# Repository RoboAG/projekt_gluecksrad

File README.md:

# projekt_gluecksrad
Bau eines elektrischen Glücksrades für schulische Veranstaltungen

Hier gibt es eine kleines [Demo-Video](https://www.youtube.com/watch?v=hORIZUaodIo&list=PL4P27g8g4QtTZY6d-4PRqTHP1PGKIp_SS) und eine [Bedienungsanleitung](Software/Keplertag_2021/README.md)([pdf](Anleitung/Anleitung_Bedienung.pdf)).

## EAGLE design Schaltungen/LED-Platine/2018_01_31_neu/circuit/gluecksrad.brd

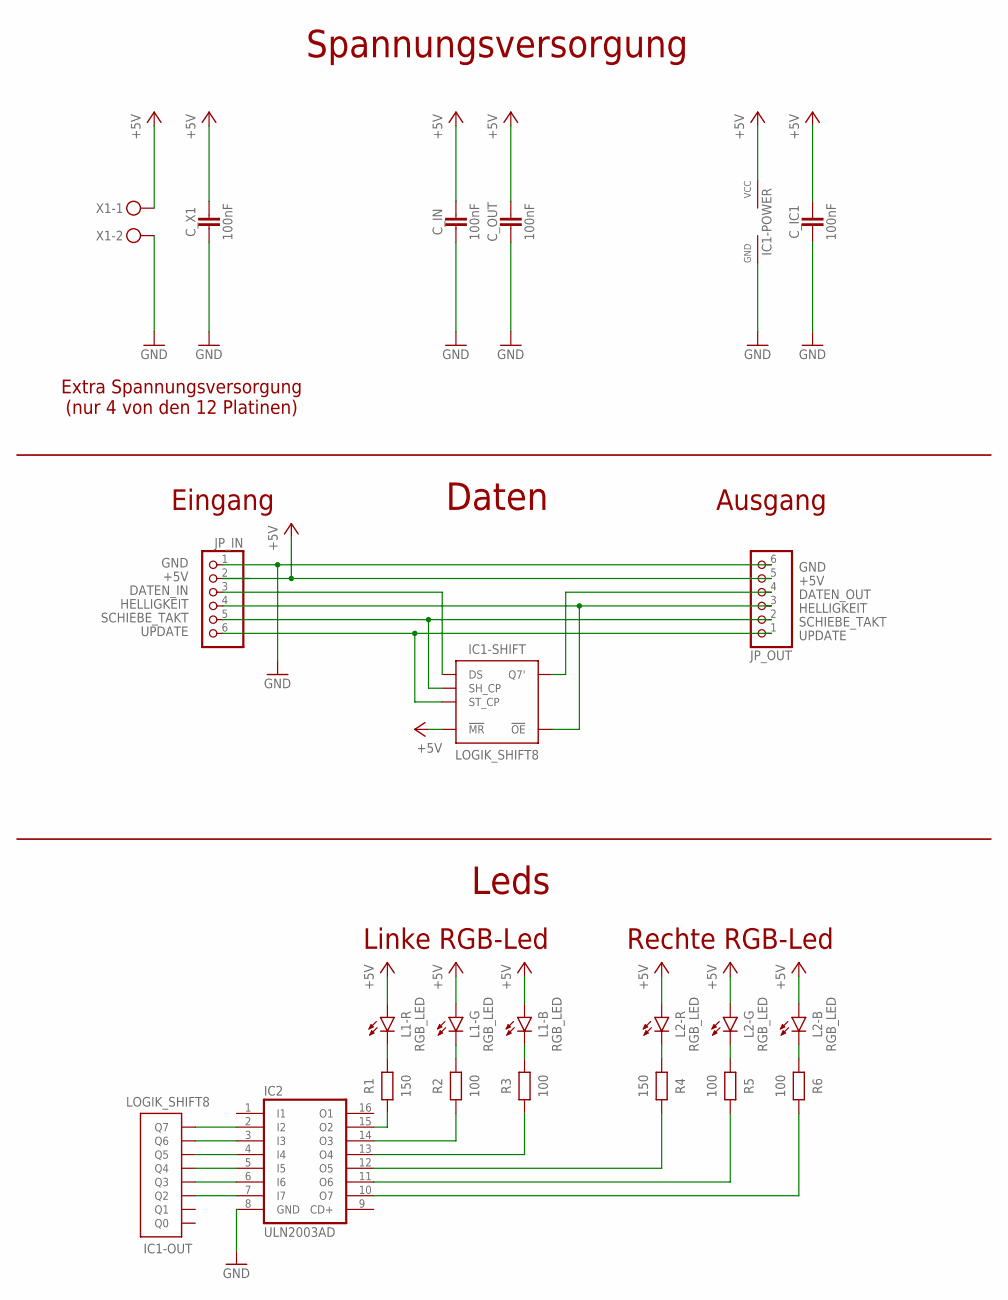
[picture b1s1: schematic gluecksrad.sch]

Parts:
C_IC1: 100nF; C_THT_2
C_IN: 100nF; C_THT_2
C_OUT: 100nF; C_THT_2
C_X1: 100nF; C_THT_2
IC1: LOGIK_SHIFT8; IC_SOIC16
IC2: ULN2003AD; SO16
JP_IN: PINHD-1X6/90; 1X06/90
JP_OUT: PINHD-1X6/90; 1X06/90
L1, L2: RGB_LED; LED_TOP_PLCC6
R1, R4: 150; R_THT_4
R2, R3, R5, R6: 100; R_THT_4
X1: STECKER_SPG_2

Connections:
+5V: C_IC1.1, C_IN.1, C_OUT.1, C_X1.1, IC1.P$10 (!MR), IC1.P$16 (VCC), JP_IN.2, JP_OUT.5, L1.1 (A), L1.3 (A), L1.4 (A), L2.1 (A), L2.3 (A), L2.4 (A), X1.1
DATEN_IN: IC1.P$14 (DS), JP_IN.3
DATEN_OUT: IC1.P$9 (Q7'), JP_OUT.4
GND: C_IC1.2, C_IN.2, C_OUT.2, C_X1.2, IC1.P$8 (GND), IC2.8 (GND), JP_IN.1, JP_OUT.6, X1.2
HELLIGKEIT: IC1.P$13 (!OE), JP_IN.4, JP_OUT.3
unnamed: IC1.P$5 (Q5), IC2.4 (I4)
unnamed: IC1.P$6 (Q6), IC2.3 (I3)
unnamed: IC1.P$2 (Q2), IC2.7 (I7)
unnamed: IC1.P$7 (Q7), IC2.2 (I2)
unnamed: IC1.P$3 (Q3), IC2.6 (I6)
unnamed: IC2.15 (O2), R1.2
unnamed: IC2.14 (O3), R2.2
unnamed: IC2.13 (O4), R3.2
unnamed: IC2.12 (O5), R4.1
unnamed: IC2.11 (O6), R5.1
unnamed: IC2.10 (O7), R6.1
unnamed: L1.6 (C), R1.1
unnamed: L1.2 (C), R2.1
unnamed: L1.5 (C), R3.1
unnamed: L2.6 (C), R4.2
unnamed: L2.2 (C), R5.2
unnamed: L2.5 (C), R6.2
unnamed: IC1.P$4 (Q4), IC2.5 (I5)
SCHIEBE_TAKT: IC1.P$11 (SH_CP), JP_IN.5, JP_OUT.2
UPDATE: IC1.P$12 (ST_CP), JP_IN.6, JP_OUT.1

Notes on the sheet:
Extra Spannungsversorgung (nur 4 von den 12 Platinen)
Eingang
Ausgang
Daten
Spannungsversorgung
Leds
Linke RGB-Led
Rechte RGB-Led

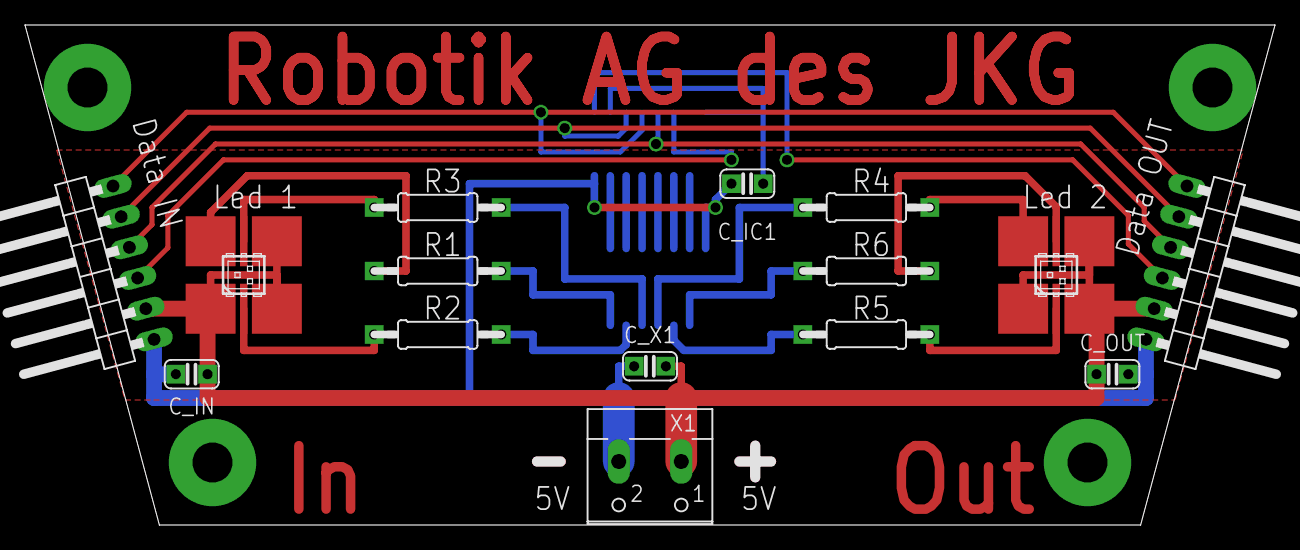
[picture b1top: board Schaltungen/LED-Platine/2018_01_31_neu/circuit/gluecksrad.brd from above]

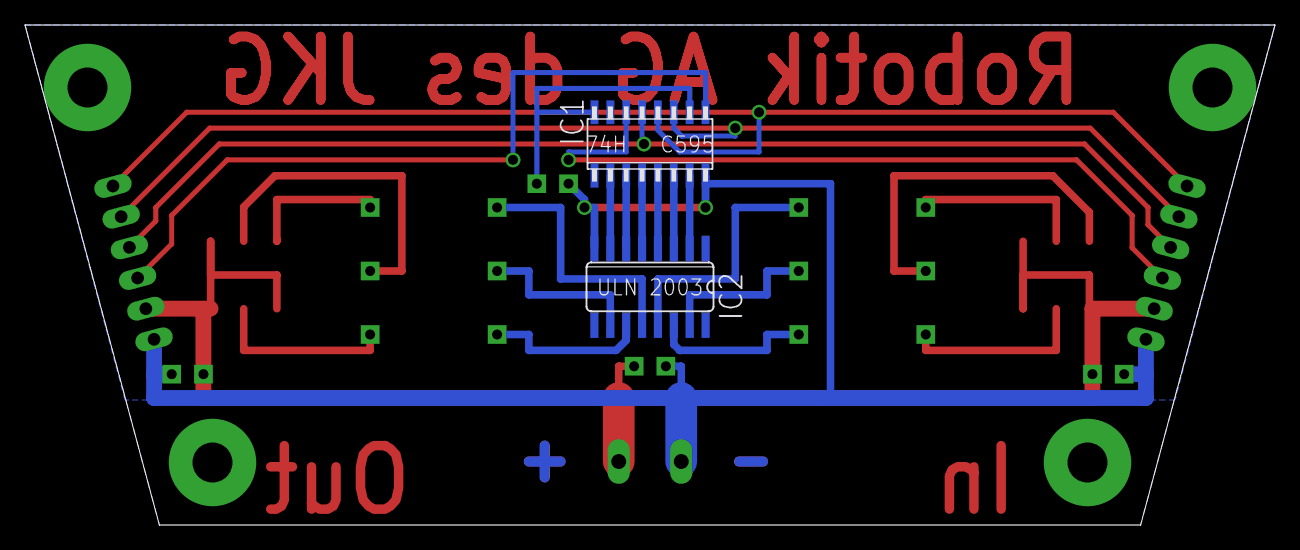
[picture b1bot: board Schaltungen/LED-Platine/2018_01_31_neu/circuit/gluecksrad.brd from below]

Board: 2 copper layers, 100.0 x 40.0 mm, 17 parts (2 on the bottom side), 25 nets.

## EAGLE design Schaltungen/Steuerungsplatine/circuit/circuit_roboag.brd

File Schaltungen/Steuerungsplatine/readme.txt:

Die Steuerungsplatine entspricht der THT-Version der Licht-Platine des RoboSAX:
    https://github.com/RoboSAX/eagle_licht

Es wird nur auf einige Bauteile bei der Bestückung verzichtet. Diese reduzierte Variante ist hier gespeichert.

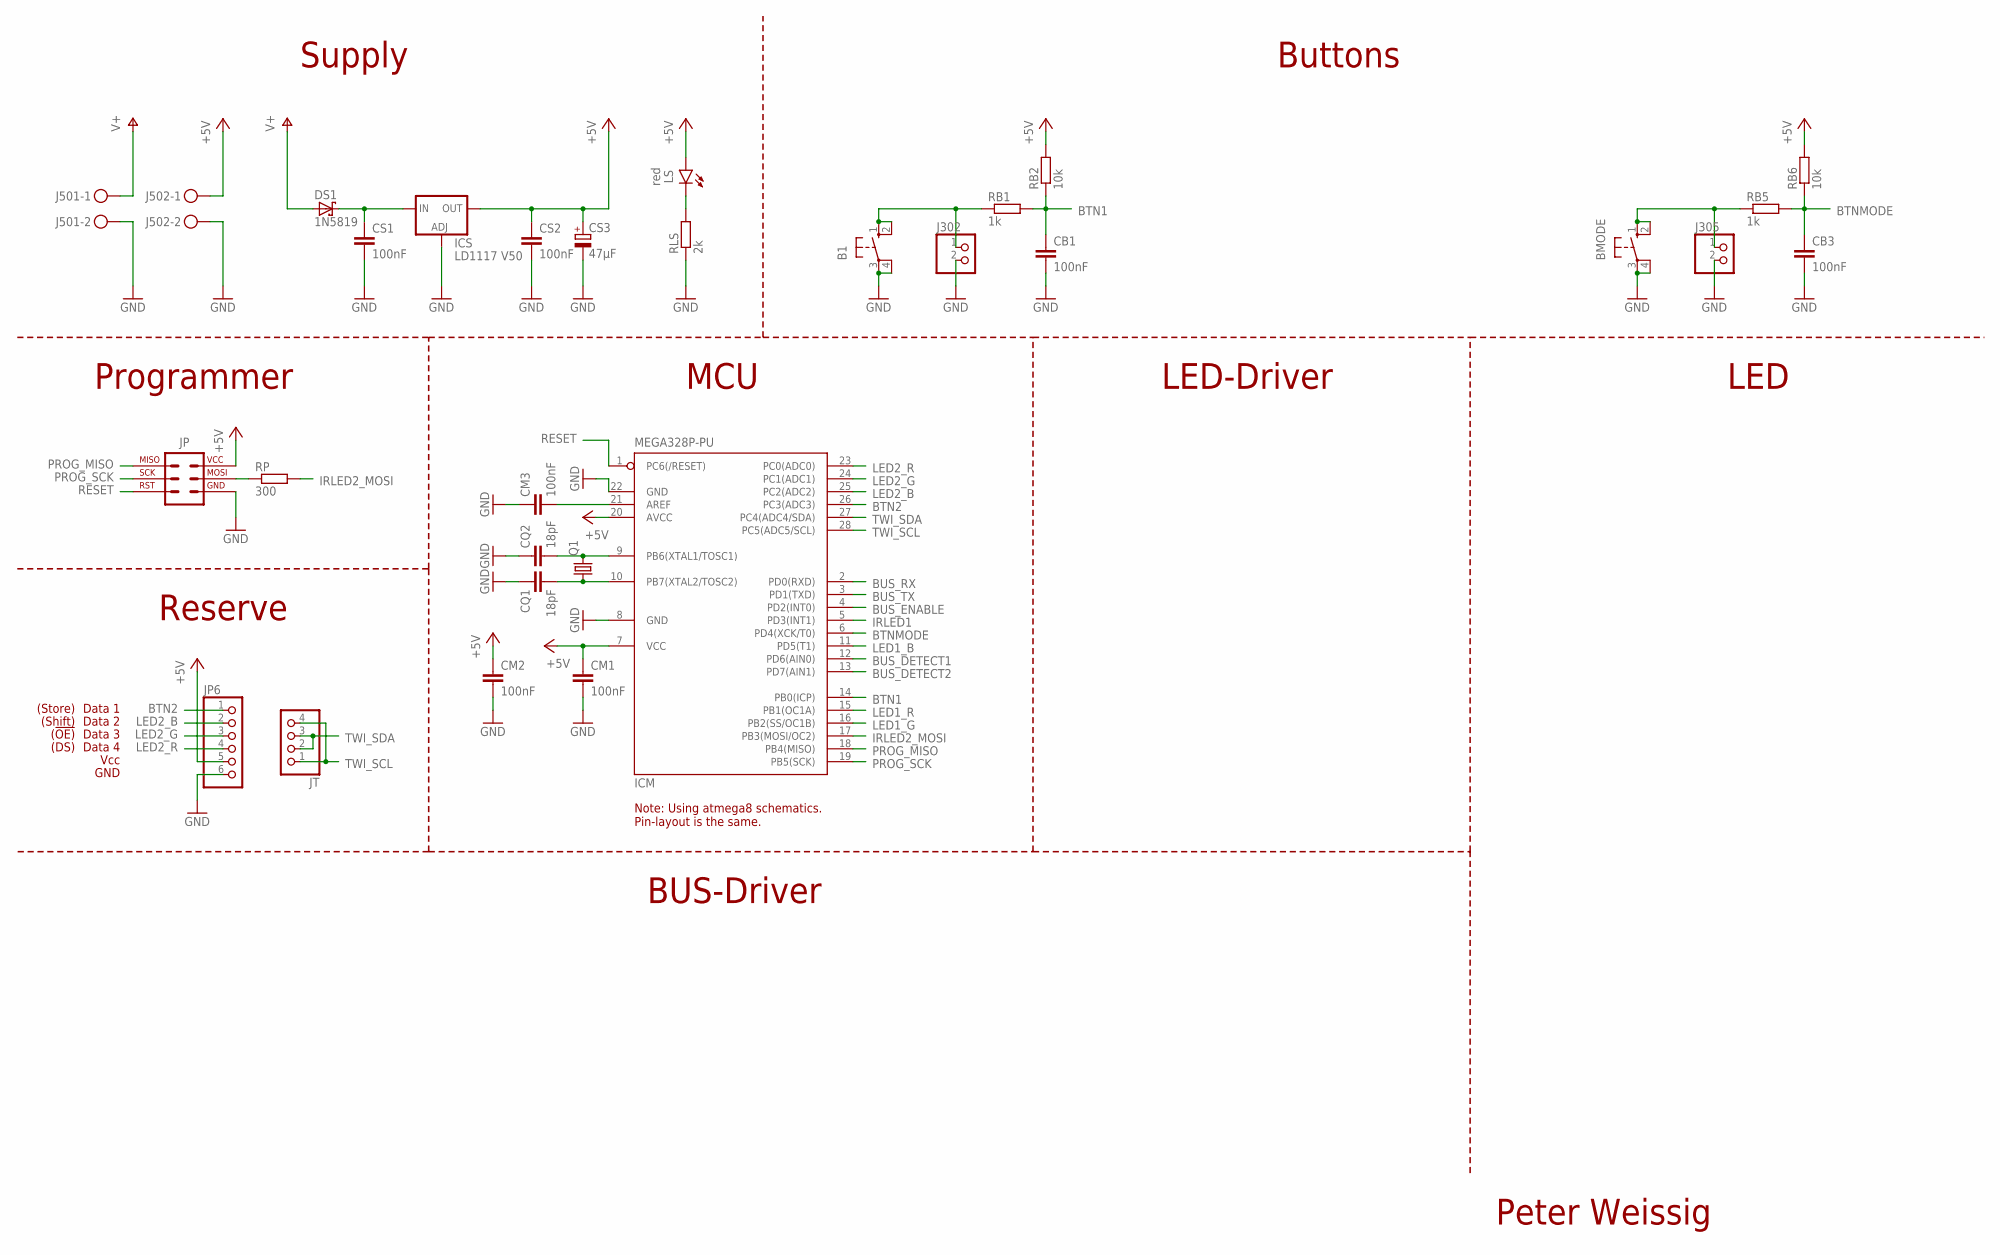
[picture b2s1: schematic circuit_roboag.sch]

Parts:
B1: 10-XX; B3F-10XX
BMODE: 10-XX; B3F-10XX
CB1, CB3: 100nF; C025-025X050
CM1, CM2, CM3: 100nF; C025-025X050
CQ1, CQ2: 18pF; C025-025X050
CS1, CS2: 100nF; C025-025X050
CS3: 47µF; E2-5
DS1: 1N5819; DO41-7.6
ICM: MEGA328P-PU; DIL28-3
ICS: LD1117 V50; TO220L1
J302, J305: PINHD-1X2; 1X02
J501, J502: STECKER_SPG_2
JP: STECKER_ISP_6; STECKER_WANNE_6
JP6: PINHD-1X6/90; 1X06/90
JT: PINHD-1X4; 1X04
LS: red; LED_3MM
Q1: CRYSTALHC49U70; HC49U70
RB1, RB5: 1k; 0207/10
RB2, RB6: 10k; 0207/10
RLS: 2k; 0207/10
RP: 300; 0207/10

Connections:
+5V: CM1.1, CM2.1, CS2.1, CS3.+, ICM.7 (VCC), ICM.20 (AVCC), ICS.2 (OUT), J502.1, JP.2 (2_VCC), JP6.5, LS.A, RB2.2, RB6.2
BTN1: CB1.1, ICM.14 (PB0(ICP)), RB1.2, RB2.1
BTN2: ICM.26 (PC3(ADC3)), JP6.1
BTNMODE: CB3.1, ICM.6 (PD4(XCK/T0)), RB5.2, RB6.1
BUS_DETECT1: ICM.12 (PD6(AIN0))
BUS_DETECT2: ICM.13 (PD7(AIN1))
BUS_ENABLE: ICM.4 (PD2(INT0))
BUS_RX: ICM.2 (PD0(RXD))
BUS_TX: ICM.3 (PD1(TXD))
GND: B1.3, B1.4 (P1), BMODE.3, BMODE.4 (P1), CB1.2, CB3.2, CM1.2, CM2.2, CM3.1, CQ1.1, CQ2.1, CS1.2, CS2.2, CS3.-, ICM.8 (GND), ICM.22 (GND), ICS.1 (ADJ), J302.2, J305.2, J501.2, J502.2, JP.6 (6_GND), JP6.6, RLS.1
IRLED1: ICM.5 (PD3(INT1))
IRLED2_MOSI: ICM.17 (PB3(MOSI/OC2)), RP.2
LED1_B: ICM.11 (PD5(T1))
LED1_G: ICM.16 (PB2(SS/OC1B))
LED1_R: ICM.15 (PB1(OC1A))
LED2_B: ICM.25 (PC2(ADC2)), JP6.2
LED2_G: ICM.24 (PC1(ADC1)), JP6.3
LED2_R: ICM.23 (PC0(ADC0)), JP6.4
unnamed: B1.1 (S), B1.2 (S1), J302.1, RB1.1
unnamed: CS1.1, DS1.C, ICS.3 (IN)
unnamed: BMODE.1 (S), BMODE.2 (S1), J305.1, RB5.1
unnamed: CQ1.2, ICM.10 (PB7(XTAL2/TOSC2)), Q1.1
unnamed: CQ2.2, ICM.9 (PB6(XTAL1/TOSC1)), Q1.2
unnamed: LS.K (C), RLS.2
unnamed: CM3.2, ICM.21 (AREF)
PROG_MISO: ICM.18 (PB4(MISO)), JP.1 (1_MISO)
PROG_MOSI_1: JP.4 (4_MOSI), RP.1
PROG_SCK: ICM.19 (PB5(SCK)), JP.3 (3_SCK)
RESET: ICM.1 (PC6(/RESET)), JP.5 (5_RST)
TWI_SCL: ICM.28 (PC5(ADC5/SCL)), JT.1, JT.4
TWI_SDA: ICM.27 (PC4(ADC4/SDA)), JT.2, JT.3
V+: DS1.A, J501.1

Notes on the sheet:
Peter Weissig
Supply
Buttons
MCU
Note: Using atmega8 schematics. Pin-layout is the same.
LED-Driver
LED
Reserve
GND
Vcc
(Store)
Data 1
Data 2
Data 3
Data 4
(Shift)
(!OE)
(DS)
Programmer
BUS-Driver

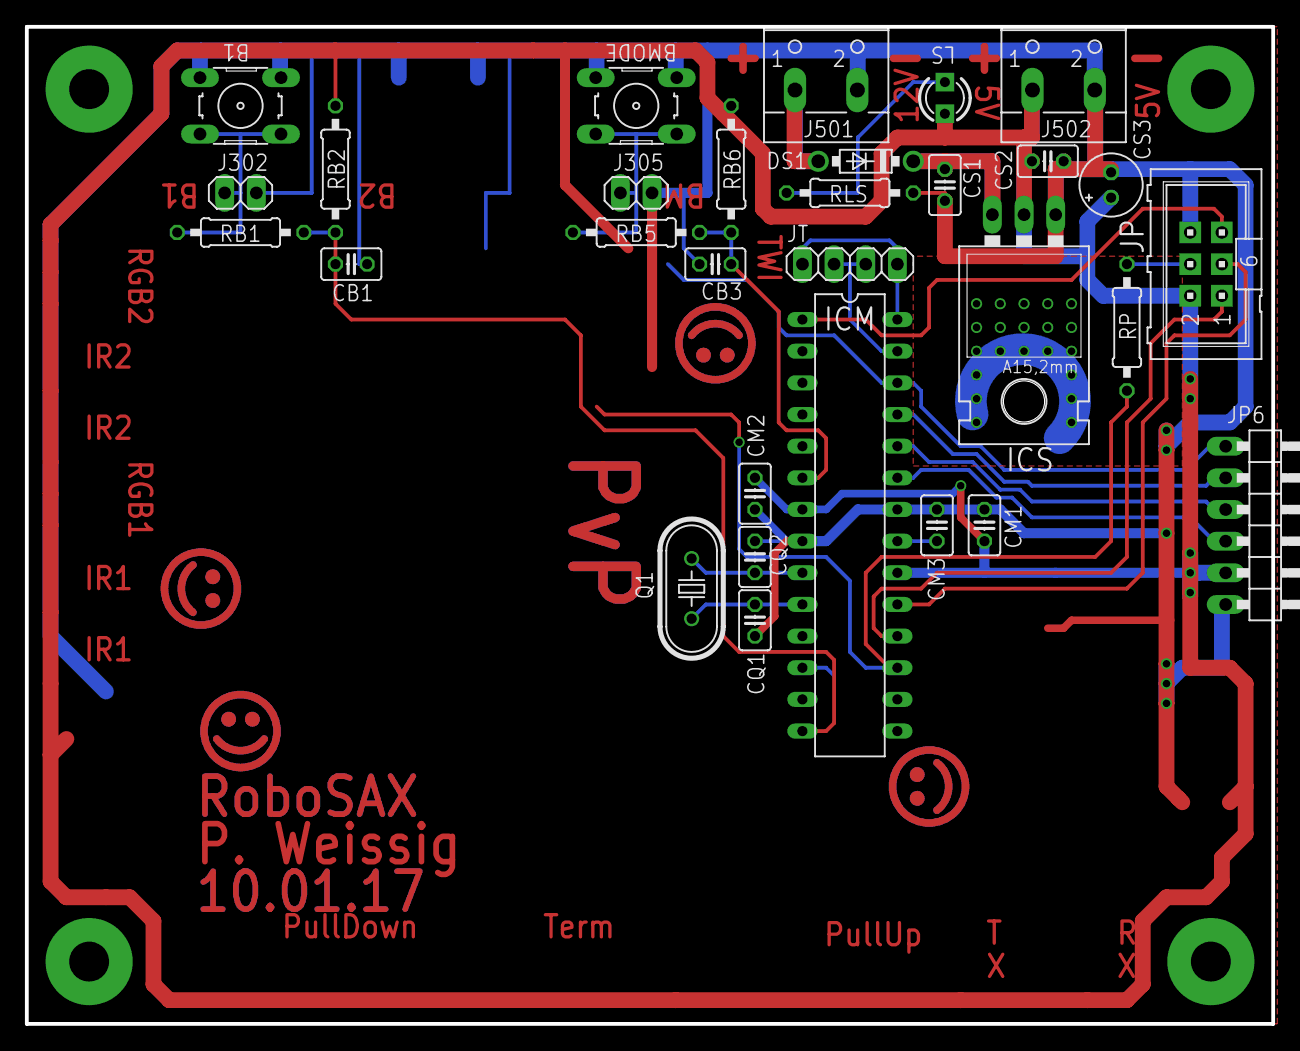
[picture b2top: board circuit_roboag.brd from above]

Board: 2 copper layers, 100.0 x 80.0 mm, 30 parts (0 on the bottom side), 23 nets.

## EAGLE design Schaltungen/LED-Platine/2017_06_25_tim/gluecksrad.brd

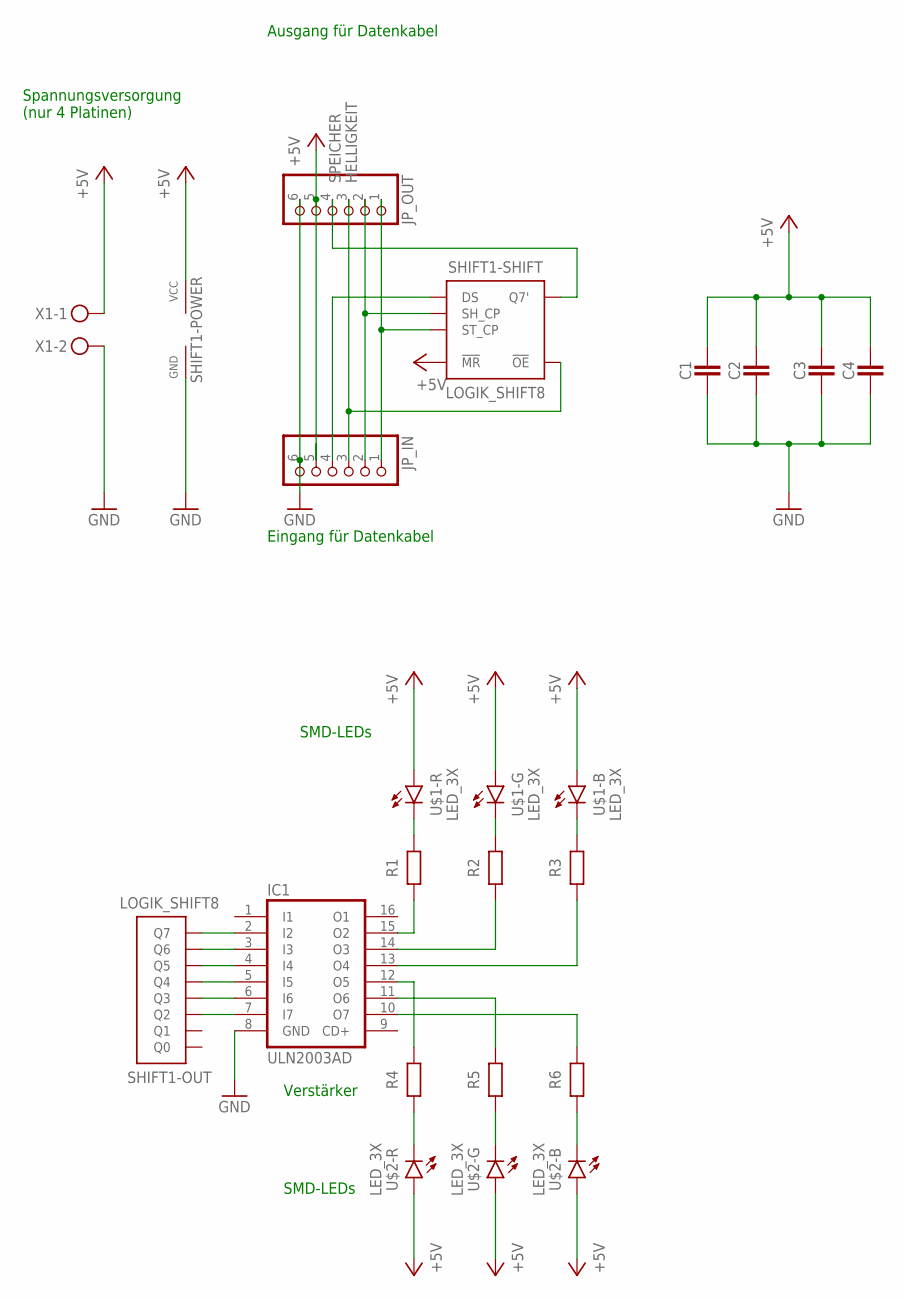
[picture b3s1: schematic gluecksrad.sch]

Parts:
C1, C3, C4: CAPACITATOR-2,5MM; C_THT_2
C2: CAPACITATOR-5MM; C_THT_3
IC1: ULN2003AD; SO16
JP_IN: PINHD-1X6/90; 1X06/90
JP_OUT: PINHD-1X6/90; 1X06/90
R1, R2, R3, R4, R5, R6: RESISTOR-10MM; R_THT_4
SHIFT1: LOGIK_SHIFT8; IC_SOIC16
U$1, U$2: LED_3X; LED_TOP_PLCC6
X1: STECKER_SPG_2

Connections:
+5V: C1.1, C2.1, C3.1, C4.1, JP_IN.5, JP_OUT.5, SHIFT1.P$10 (!MR), SHIFT1.P$16 (VCC), U$1.1 (A), U$1.3 (A), U$1.4 (A), U$2.1 (A), U$2.3 (A), U$2.4 (A), X1.1
GND: C1.2, C2.2, C3.2, C4.2, IC1.8 (GND), JP_IN.6, JP_OUT.6, SHIFT1.P$8 (GND), X1.2
HELLIGKEIT: JP_IN.3, JP_OUT.3, SHIFT1.P$13 (!OE)
unnamed: IC1.4 (I4), SHIFT1.P$5 (Q5)
unnamed: IC1.3 (I3), SHIFT1.P$6 (Q6)
unnamed: IC1.7 (I7), SHIFT1.P$2 (Q2)
unnamed: IC1.2 (I2), SHIFT1.P$7 (Q7)
unnamed: IC1.6 (I6), SHIFT1.P$3 (Q3)
unnamed: IC1.15 (O2), R1.2
unnamed: IC1.14 (O3), R2.2
unnamed: IC1.13 (O4), R3.2
unnamed: IC1.12 (O5), R4.1
unnamed: IC1.11 (O6), R5.1
unnamed: IC1.10 (O7), R6.1
unnamed: R1.1, U$1.6 (C)
unnamed: R2.1, U$1.2 (C)
unnamed: R3.1, U$1.5 (C)
unnamed: R4.2, U$2.6 (C)
unnamed: R5.2, U$2.2 (C)
unnamed: R6.2, U$2.5 (C)
unnamed: IC1.5 (I5), SHIFT1.P$4 (Q4)
unnamed: JP_OUT.4, SHIFT1.P$9 (Q7')
unnamed: JP_IN.4, SHIFT1.P$14 (DS)
unnamed: JP_IN.2, JP_OUT.2, SHIFT1.P$11 (SH_CP)
SPEICHER: JP_IN.1, JP_OUT.1, SHIFT1.P$12 (ST_CP)

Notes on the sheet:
Spannungsversorgung (nur 4 Platinen)
Eingang für Datenkabel
Ausgang für Datenkabel
SMD-LEDs
Verstärker

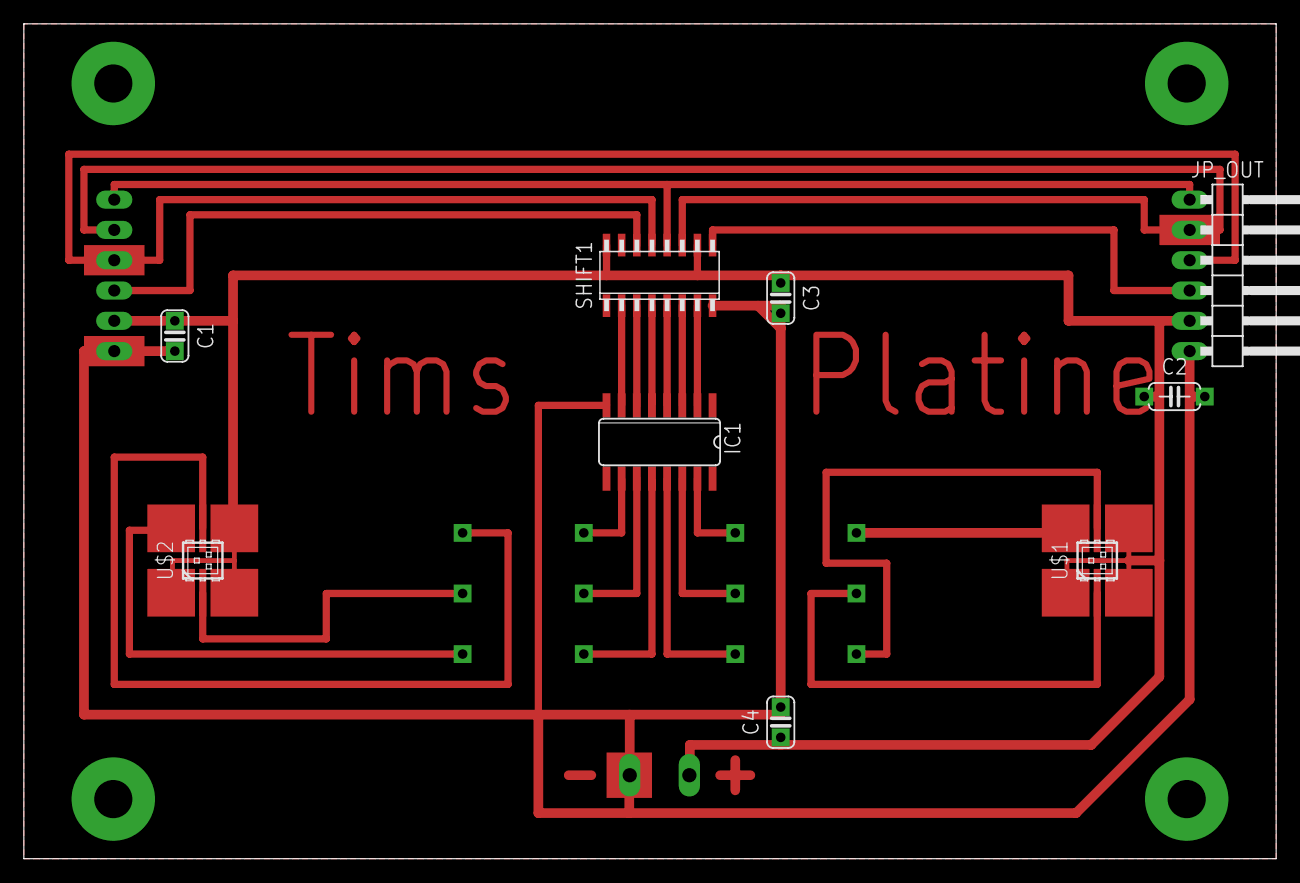
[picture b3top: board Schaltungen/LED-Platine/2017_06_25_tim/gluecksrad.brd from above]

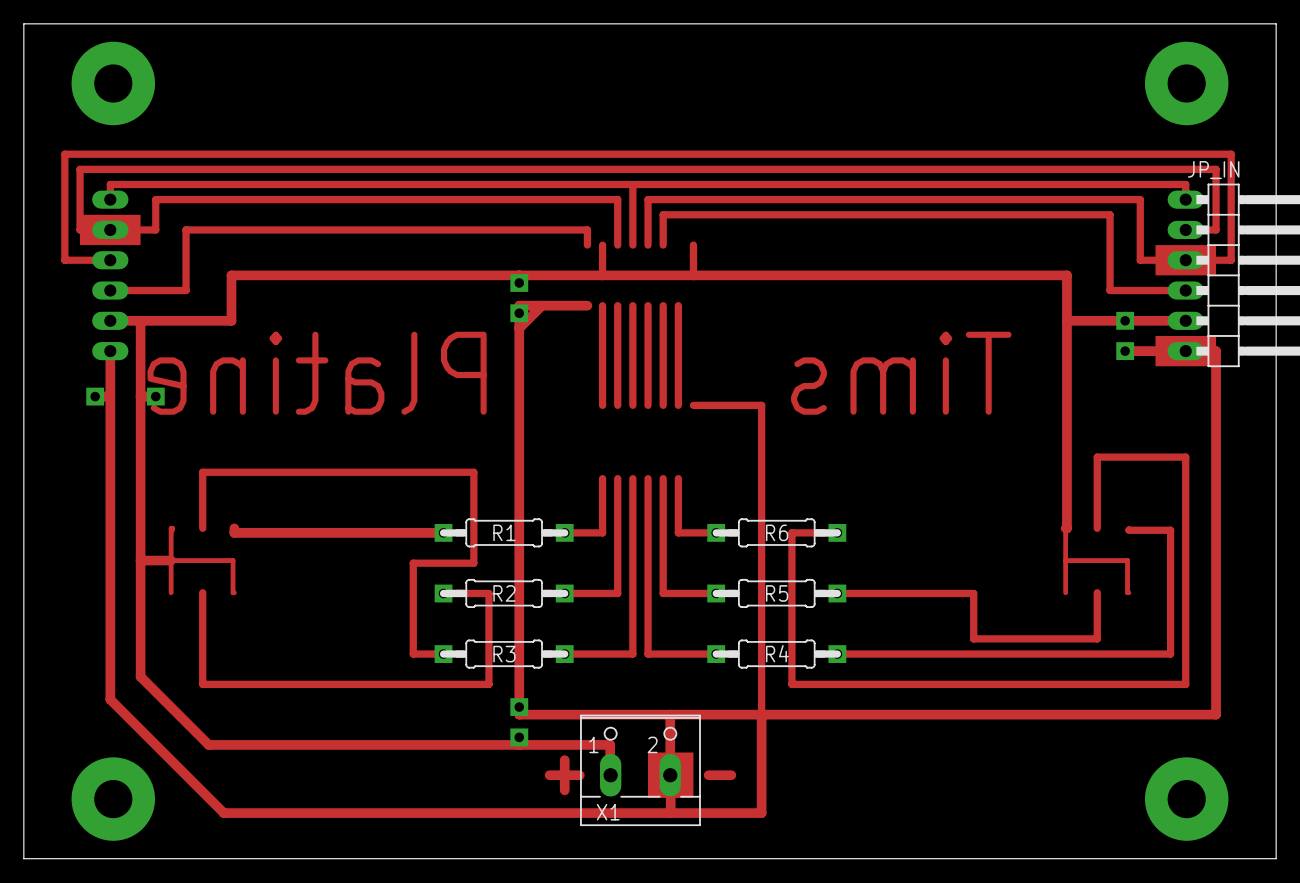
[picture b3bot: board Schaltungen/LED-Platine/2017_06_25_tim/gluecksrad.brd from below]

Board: 2 copper layers, 105.0 x 70.0 mm, 17 parts (8 on the bottom side), 25 nets.

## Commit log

2018-02-01 adeed circuit files (made with eagle)
2018-02-01 added simple software tests
2018-02-16 added todo-list
2018-02-17 added picture of principal arrangement of circuit boards
2018-03-02 updated LED-Platine (added values for resistors)
2018-03-02 moved circuit for LED-Platine to dedicated subfolder
2018-03-02 added Steuerungsplatine (copy from https://github.com/RoboSAX/eagle_licht.git)
2018-03-02 updated LED-Platine (resistor for red is 150R not 120R)
2018-03-02 renamed Tests/ to devel/
2018-03-02 added Source-Code from Richard
2018-03-06 Create lichter_demo.c from Tim's source
2018-03-07 fixed devel-software (richard test datenbus)
2018-03-07 added Initialisierung (copy from robosax/avr_licht.git)
2018-03-07 added Skizze + kleine Vorschau für readme.md + allgemeine Skizze noch ohne Maße
2018-03-07 added Gedanken zur Platinenanzahl (10 scheint optimal)
2018-03-07 added picture of latest development
2018-03-11 added Bild Entwicklungsstand 11.03.2018 (stehendes Stativ)
2018-03-12 updated Zeichnung
2018-03-13 added initial source code alex
2018-03-14 Updated alex test_datenbus main
2018-03-14 fixed typo error
2018-03-15 added Travis-files for continuous integration tests
2018-03-15 bugfix to travis files
2018-03-15 bugfixed travis job
2018-03-15 updated travis files
2018-03-15 bugfix for travis job
2018-03-15 bugfixes
2018-03-15 bugfix
2018-03-16 removed wrong spaces
2018-03-16 bugfixed files
2018-03-18 added second LED API variant
2018-03-18 changed readme files
2018-03-18 added random test
2018-03-18 updated led_api 1
2018-03-18 added button test
2018-03-18 fixed bugs
2018-03-18 added eeprom test
2018-03-18 fixed eeprom import
2018-03-19 fixed led api 1
    bug: board order 2-1 instead of 1-2 (2-1-4-3-6-5-8-7)
2018-03-19 changed button test
    use all leds for testing
2018-03-19 fixed button macros
2018-03-19 applied macro changes
2018-03-20 updated travis-job + updated builds for devel/alex
2018-03-20 added timer to devel/alex
2018-03-21 renamed devel directories
2018-03-21 added devel/Peter
2018-03-21 added buttons.h
2018-03-21 added leds2/ to devel/peter
2018-03-21 added missing file (buttons.h)
2018-03-21 added cover to devel/peter & bugfixed systick_delay() in led2
2018-03-22 added non-debugged Gluecksrad code
    ATTENTION: NOT DEBUGGED!!!
    new api changes of Peter has to be applied
2018-03-22 added random to devel/peter
2018-03-22 changed file structure within devel/peter
2018-03-22 updated travis-job (echos name of current folder while building all tests)
2018-03-22 added missing file (.gitignore)
2018-03-22 minor formating changes
2018-03-22 added devel/main + added modules + moved alex/gluecksrad to main/freuhlingsmarkt + bugfixes within main.c
2018-03-22 formatted gluecksrad main
2018-03-22 added glkrad_main to travis build
2018-03-22 added header link
2018-03-22 added prices empty handler
2018-03-23 added Pinbelegung
2018-03-23 changed rotation end animation
2018-03-23 fixed rotation end animation 2
2018-03-24 added tests from RoboAG 23.3.2018
2018-03-24 added differrent animations, fixed prices bug
2018-03-24 added atmega specification file
2018-03-24 changed animations
2018-03-24 added 1s delay before reset animation shows
2018-03-24 Make getRotationTarget() more random
2018-03-24 not much done
2018-03-24 changed random test
2018-03-24 many fixes
    switched names of PRICES_MAX and PRICES_COUNT
    added missing breeak; statements
    changed price type to signed integer
    updated getRotatinTarget function. Not compleately tested!
2018-03-24 Corrected Alex's mistakes
2018-03-24 minor fix
2018-03-24 minor fixes
2018-03-24 fixed getRotationTarget
2018-03-25 added DEFAULT and LENZ mode
    default: DEFAULT
    hold btnMode on startup to switch to LENZ mode
2018-03-25 added folder for menu version
2018-03-25 added menu feature
2018-03-25 updated readme of main and main_menu
2018-03-25 reorganized source-code files
2018-03-25 updated travis job to new file structure
2018-03-25 added missing header files (as links)
2018-03-26 formatting adjustments
2018-03-26 Revert "formatting adjustments"
    This reverts commit e3defc1c7a93ed022443bbb679748349dea71776.
2018-03-26 added semicolon
2018-03-26 added all sketch files
2018-04-04 updated drawing & added link for demo-video
2018-04-13 added menu show prices
2018-04-20 fixed eeprom output
2018-05-04 removed show prices menu
2018-11-02 updated .gitignore files + removed single ignore files within software + added main ignore file to software + corrected ignore file for Datenblaetter/
2018-11-02 updated readme files + alex updated Frühlingsmarkt + renamed readme.txt in Initialisierung/ + updated main readme to link to explanation of Frühlingsmarkt
2019-02-04 added notifications to .travis.yml
2019-02-07 fixed name for devel/tim...
2019-02-07 fixed typo
2019-02-07 simplified file structure within Initialisierung
2019-02-07 added Makefiles for build tests
2019-02-07 updated travis - job (it's now only one hidden bash script)
2019-02-07 removed old travis bash scripts
2019-02-09 added Fruehlingsmarkt_2019
2019-02-09 applied changes for Fruehlingsmarkt 2019
2019-02-22 updated wheel documentation switched white <-> yellow
2019-02-25 updated version number
2021-09-25 fixed minor warning
2021-09-25 updated Makefiles + added Fruehlingsmarkt_2019/ to default build + minor fix to main Makefile + replaced 2-level Makefiles with a more generic version
2021-09-25 added precompiled hex-files for Frühlingsmarkt 2018/2019
2021-09-25 added Erklärdiagramme
2021-09-25 updated 2nd level Makefile to ignore modules/ & common/
2021-09-26 moved glueckrad.ini to modules/
2021-09-26 copied files for Keplertag 2021 (not changes yet)
2021-09-26 added minor changes from Jasper/Peter + debounce of mode-button in menu state + some changes for testing (e.g. price count)
2021-09-26 fixed main.c (removed unused functions)
2021-09-26 added updated Version of readme.md for Keplertag (also changed link from main readme to here)
2021-09-26 updated main.c (renamed some variables/constants) + time_cur --> time_now + time_anim_start --> time_state_start + LENZ --> COUNTDOWN + replaced some (time) constants with defines + changed EEPROM ke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
2021-09-26 added global variable for maximum/initial number of prices
2021-09-26 added some comments
2021-09-26 moved (const) variable prices_max to const section
2021-09-26 many changes to main.c! + removed unnecessary lines + updated color definitions (using 0 instead of LEDS_MIN) + renamed some states to improve readability + added/moved more delay values as defines +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
2021-09-26 splitted main file into common main.c and wrapper.c
2021-09-26 added old events
2021-10-08 minor fix to animation
2021-10-08 moved price definition from main.c to wrapper.c
2021-10-08 Aktualisierung des Glücksrades für den Keplertag 2021 ~ Anordnung der Preise (sichtbar auf dem Glücksrad) ~ interne Preisanzahl
2021-10-08 updated Start-Diagramm
2021-10-08 Bedienungsanleitung zum Ausdrucken erstellt
2021-10-08 corrected typo in price count (750 instead of 150)
2021-10-10 fixed orientation of wheel of fortune
